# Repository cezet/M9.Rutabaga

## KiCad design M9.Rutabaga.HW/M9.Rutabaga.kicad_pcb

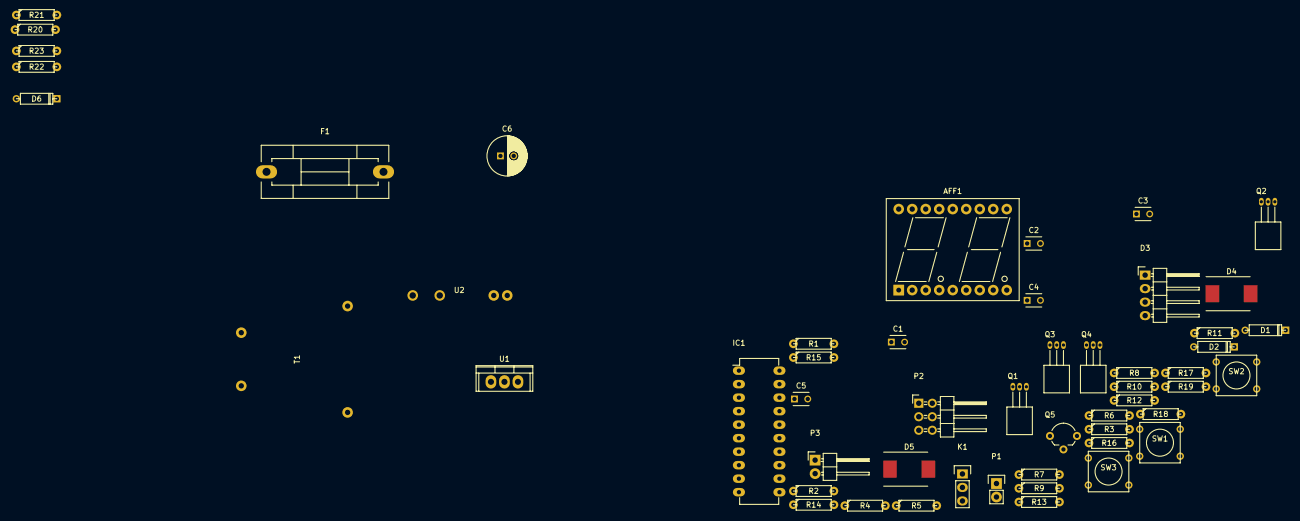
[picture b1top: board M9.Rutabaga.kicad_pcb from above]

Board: 2 copper layers, 53 parts (0 on the bottom side), 44 nets, no tracks yet.

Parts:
AFF1: FYD-5621FE; DA56
C1, C4, C5: 100n; C_Disc_D3_P2.5
C2: 0u33; C_Disc_D3_P2.5
C3: 0u1; C_Disc_D3_P2.5
C6: 220u; C_Radial_D7.5_L11.2_P2.5
D1, D2: LED; D3
D3: BRIDGE; Pin_Header_Angled_1x04
D4: Led_Small; DO-214AB
D5: D_Schottky_Small; DO-214AB
D6: ZENERsmall; D3
F1: F_Small; Fuseholder5x20_horiz_SemiClosed_Casing10x25mm
IC1: ATTINY2313A-P; DIP-20_W7.62mm_LongPads
K1: CONN_3; Pin_Header_Straight_1x03
P1: CONN_2; Pin_Header_Straight_1x02
P2: CONN_3X2; Pin_Header_Angled_2x03
P3: CONN_01X02; Pin_Header_Angled_1x02
Q1, Q2: BC817-40; TO-92_Horizontal1_Inline_Narrow_Oval
Q3, Q4: BC556; TO-92_Horizontal1_Inline_Narrow_Oval
Q5: BC549; TO-92_Molded_Wide_Reverse
R1, R3: 220; R3-LARGE_PADS
R2, R4, R5, R6, R9, R18, R19: 10k; R3-LARGE_PADS
R7: 330; R3-LARGE_PADS
R8: 47k; R3-LARGE_PADS
R10, R11, R12, R13, R14, R15, R16, R17: 82; R3-LARGE_PADS
R20, R21, R22, R23: 100; R3-LARGE_PADS
SW1, SW2, SW3: DPST; SW_PUSH_SMALL
T1: TRANSFO; TEZ_20D
U1: 7805; TO-220
U2: FRM18

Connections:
+5V: C3.1, D4.2, D5.1, IC1.20, K1.1, P2.2, Q3.3, Q4.3, R1.1, R2.1, R3.1, R4.1, R5.1, R8.1, R18.1, R19.1, U1.3, U2.1
/AC_L1: F1.1, P1.2, U2.3
/AC_L1_OUT: P3.1, U2.4
/AC_N: P1.1, P3.2
/ANOD1: IC1.7, Q3.2, R4.2
/ANOD2: IC1.8, Q4.2, R5.2
/BUT1: C4.1, IC1.2, R19.2, SW3.1
/BUT2: C5.1, IC1.3, R18.2, SW2.1
/DS18: IC1.9, K1.2, R8.2
/LED1: IC1.4, Q1.1
/LED2: IC1.5, Q2.1
/LED7_B: AFF1.10, AFF1.15, R12.1
/LED7_C: AFF1.3, AFF1.8, R14.1
/LED7_D: AFF1.2, AFF1.6, R15.1
/LED7_DP: AFF1.4, AFF1.9, R13.1
/LED7_E: AFF1.1, AFF1.5, R16.1
/LED7_F: AFF1.12, AFF1.18, R17.1
/LED7_G: AFF1.7, AFF1.17, R11.1
/LED_7A: AFF1.11, AFF1.16
/MISO: IC1.18, R11.2, R20.2
/MOSI: IC1.17, R17.2, R23.1
/SCK: IC1.19, R13.2, R21.2
/~RESET: C1.1, IC1.1, R2.2, R22.2, SW1.2
GND: C1.2, C2.2, C3.2, C4.2, C5.2, C6.2, D3.1, D6.2, IC1.10, K1.3, P2.6, Q1.2, Q2.2, Q5.3, R9.2, SW1.1, SW2.2, SW3.2, U1.2
unnamed: AFF1.13, Q3.1
unnamed: AFF1.14, Q4.1
unnamed: C2.1, C6.1, D3.3, D6.1, U1.1
unnamed: D1.1, R1.2
unnamed: D1.2, Q1.3
unnamed: D2.1, R3.2
unnamed: D2.2, Q2.3
unnamed: D4.1, R7.2
unnamed: D5.2, Q5.1, R7.1, U2.2
unnamed: F1.2, T1.1
unnamed: IC1.12, R10.2
unnamed: IC1.13, R12.2
unnamed: IC1.14, R14.2
unnamed: IC1.15, R15.2
unnamed: IC1.16, R16.2
unnamed: P2.1, R20.1
unnamed: P2.3, R21.1
unnamed: P2.4, R23.2
unnamed: P2.5, R22.1
unnamed: Q5.2, R6.1, R9.1

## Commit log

2015-06-21 :octocat: Added .gitattributes
2015-06-21 First sync
2015-11-01 HW RC1
    Hardware rc1
